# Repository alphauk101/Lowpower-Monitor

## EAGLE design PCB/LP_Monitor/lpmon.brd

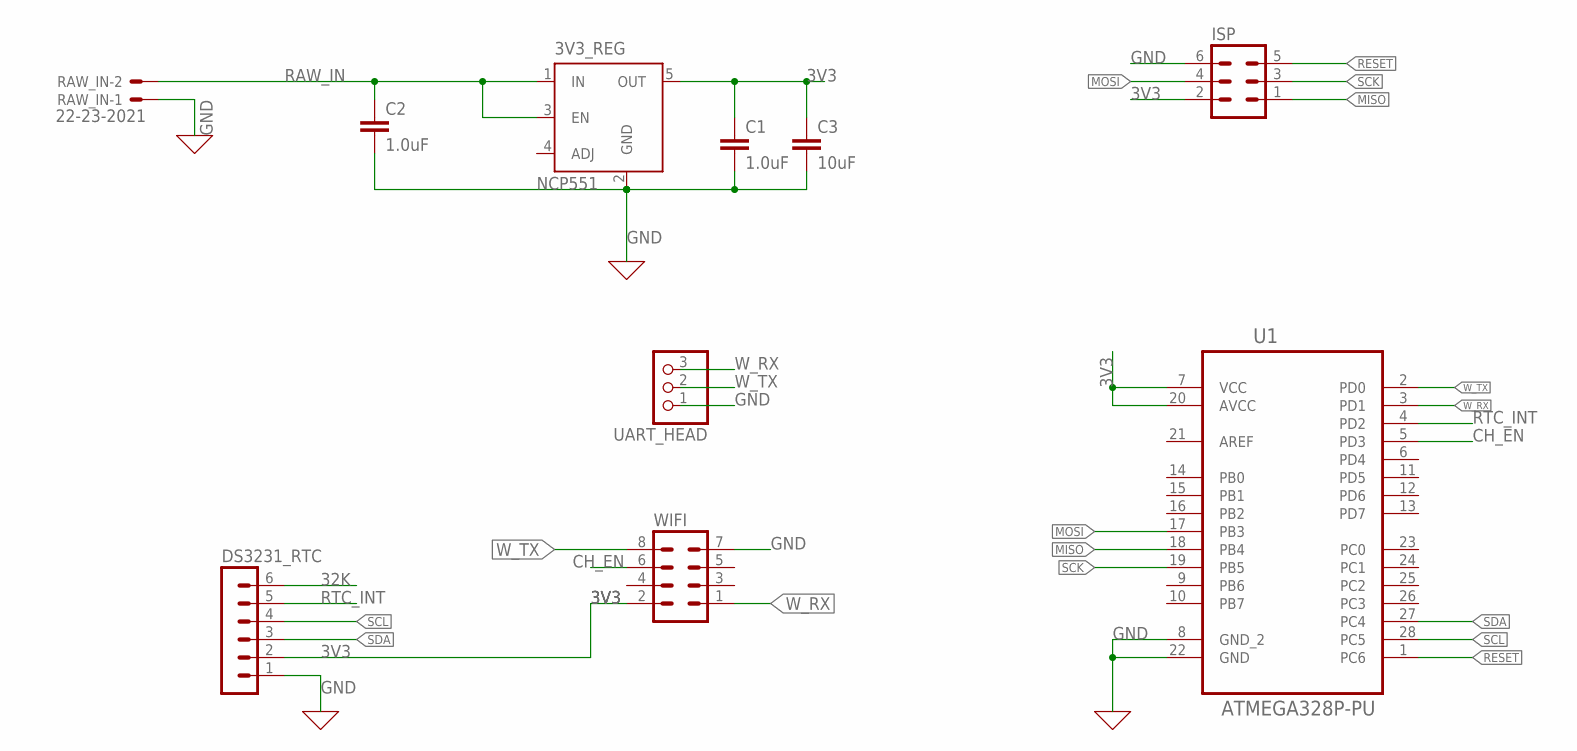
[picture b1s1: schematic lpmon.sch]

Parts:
3V3_REG: NCP551; SOT23-5
C1, C2: 1.0uF; C2.5-2
C3: 10uF; C2.5-2
DS3231_RTC: MA06-1
ISP: MA03-2
RAW_IN: 22-23-2021
U1: ATMEGA328P-PU; DIP254P762X457-28
UART_HEAD: PINHD-1X3; 1X03
WIFI: MA04-2

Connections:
3V3: 3V3_REG.5 (OUT), C1.1, C3.1, DS3231_RTC.2, ISP.2, U1.7 (VCC), U1.20 (AVCC), WIFI.2
32K: DS3231_RTC.6
CH_EN: U1.5 (PD3), WIFI.6
GND: 3V3_REG.2 (GND), C1.2, C2.2, C3.2, DS3231_RTC.1, ISP.6, RAW_IN.1, U1.8 (GND_2), U1.22 (GND), UART_HEAD.1, WIFI.7
MISO: ISP.1, U1.18 (PB4)
MOSI: ISP.4, U1.17 (PB3)
RAW_IN: 3V3_REG.1 (IN), 3V3_REG.3 (EN), C2.1, RAW_IN.2
RESET: ISP.5, U1.1 (PC6)
RTC_INT: DS3231_RTC.5, U1.4 (PD2)
SCK: ISP.3, U1.19 (PB5)
SCL: DS3231_RTC.4, U1.28 (PC5)
SDA: DS3231_RTC.3, U1.27 (PC4)
W_RX: U1.3 (PD1), UART_HEAD.3, WIFI.1
W_TX: U1.2 (PD0), UART_HEAD.2, WIFI.8

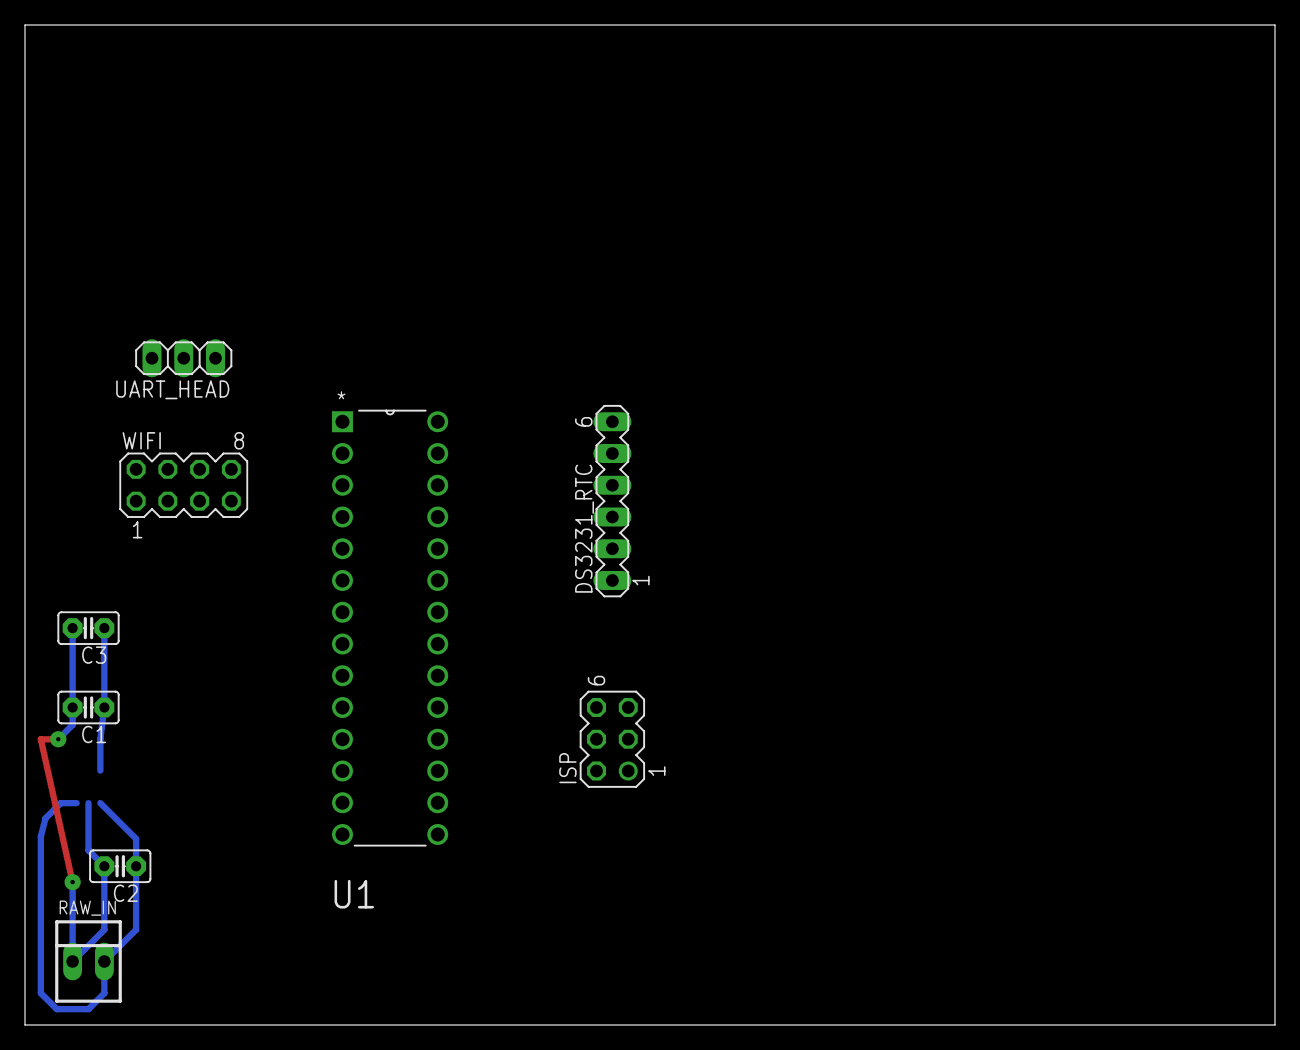
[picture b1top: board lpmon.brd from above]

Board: 2 copper layers, 100.0 x 80.0 mm, 10 parts (1 on the bottom side), 13 nets.

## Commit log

2018-12-30 Adding Schematic
2018-12-31 Arduino low power librarires
2018-12-31 more
2018-12-31 updates to pcb
2019-01-01 started pcb
